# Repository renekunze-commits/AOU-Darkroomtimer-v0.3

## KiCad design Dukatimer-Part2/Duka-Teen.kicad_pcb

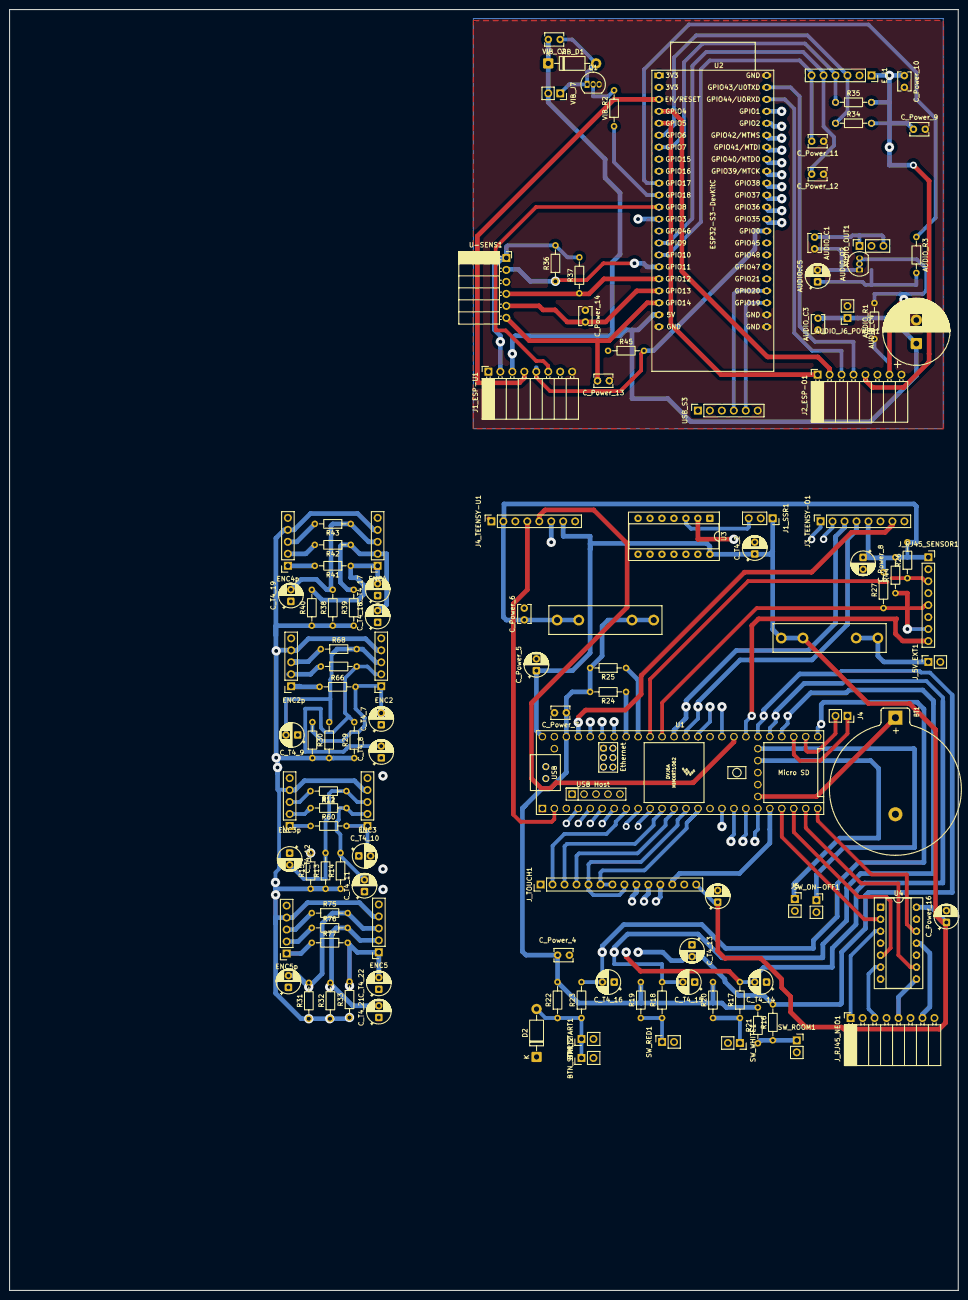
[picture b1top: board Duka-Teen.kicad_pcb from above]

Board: 6 copper layers, 201.3 x 271.8 mm, 122 parts (0 on the bottom side), 89 nets.

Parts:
AUDIO:C5: 10µF; CP_Radial_D5.0mm_P2.50mm
AUDIO_C1: 10nF; C_Disc_D3.8mm_W2.6mm_P2.50mm
AUDIO_C3: 100nF; C_Disc_D3.8mm_W2.6mm_P2.50mm
AUDIO_C4: 1000µF; CP_Radial_D14.0mm_P5.00mm
AUDIO_J6_POWER1: Conn_01x02_Socket; PinSocket_1x02_P2.54mm_Vertical
AUDIO_OUT1: Conn_01x03_Socket; PinSocket_1x03_P2.54mm_Vertical
AUDIO_Q2: BC337; TO-92_Inline
AUDIO_R1: 1k; R_Axial_DIN0204_L3.6mm_D1.6mm_P7.62mm_Horizontal
AUDIO_R3: 10k; R_Axial_DIN0204_L3.6mm_D1.6mm_P7.62mm_Horizontal
BT1: Battery_Cell; BatteryHolder_Keystone_106_1x20mm
BTN_START1, BTN_START2: Conn_01x02_Socket; PinHeader_1x02_P2.54mm_Vertical
C_Power_4, C_Power_6, C_Power_7, C_Power_9, C_Power_10: 100nF; C_Disc_D3.8mm_W2.6mm_P2.50mm
C_Power_5, C_Power_8: 10µF; CP_Radial_D5.0mm_P2.50mm
C_Power_11, C_Power_12, C_Power_13, C_Power_14: NC; C_Disc_D3.8mm_W2.6mm_P2.50mm
C_Power_15, C_Power_16: 100nF; CP_Radial_D5.0mm_P2.50mm
C_T4_2, C_T4_7, C_T4_8, C_T4_9, C_T4_10, C_T4_12, C_T4_13, C_T4_14, C_T4_15, C_T4_16, C_T4_17, C_T4_18, C_T4_19, C_T4_20, C_T4_21, C_T4_22: 100nF; CP_Radial_D5.0mm_P2.50mm
C_T4_11: 10nF; CP_Radial_D5.0mm_P2.50mm
D2: TVS NC; D_DO-41_SOD81_P10.16mm_Horizontal
ENC2, ENC2p, ENC3, ENC3p, ENC4, ENC4p, ENC5, ENC5p: Conn_01x05_Socket; PinSocket_1x05_P2.54mm_Vertical
E_J1: Conn_01x06_Socket; PinSocket_1x06_P2.54mm_Vertical
F3: Fuse_Small; Fuseholder_Littelfuse_100_series_5x20mm
F_5V_EXT1: Fuse_Small; Fuseholder_Littelfuse_100_series_5x20mm
J1_ESP-U1, J2_ESP-O1: Conn_01x08_Socket; PinSocket_1x08_P2.54mm_Horizontal
J1_SSR1: Conn_01x03_Socket; PinSocket_1x03_P2.54mm_Vertical
J3_TEENSY-O1, J4_TEENSY-U1: Conn_01x08_Pin; PinSocket_1x08_P2.54mm_Vertical
J4, J5: Conn_01x02_Socket; PinSocket_1x02_P2.54mm_Vertical
J_5V_EXT1: Screw_Terminal_01x02; PinSocket_1x02_P2.54mm_Vertical
J_RJ45_NEO1: Conn_01x08_Socket; PinSocket_1x08_P2.54mm_Horizontal
J_RJ45_SENSOR1: Conn_01x08_Socket; PinSocket_1x08_P2.54mm_Vertical
J_TOUCH1: Conn_01x14_MountingPin; PinHeader_1x14_P2.54mm_Vertical
Q1: BC337; TO-92_Inline
R11, R12, R41, R42, R43, R60, R66, R67, R68, R75, R76, R77: 100; R_Axial_DIN0204_L3.6mm_D1.6mm_P7.62mm_Horizontal
R13, R19, R20, R21, R22, R24, R25, R26, R27, R28, R29, R30, R33, R38, R45: 10k; R_Axial_DIN0204_L3.6mm_D1.6mm_P7.62mm_Horizontal
R14, R15, R31, R32, R34, R35, R36, R37: NC; R_Axial_DIN0204_L3.6mm_D1.6mm_P7.62mm_Horizontal
R16, R17, R18: 0.8k-2k; R_Axial_DIN0204_L3.6mm_D1.6mm_P7.62mm_Horizontal
R23: 1k-4.7k; R_Axial_DIN0204_L3.6mm_D1.6mm_P7.62mm_Horizontal
R39, R40: 0; R_Axial_DIN0204_L3.6mm_D1.6mm_P7.62mm_Horizontal
R44: 4.7k; R_Axial_DIN0204_L3.6mm_D1.6mm_P7.62mm_Horizontal
SW_ON-OFF1: Conn_01x02_Socket; PinSocket_1x02_P2.54mm_Vertical
SW_RED1: Conn_01x02_Socket; PinSocket_1x02_P2.54mm_Vertical
SW_ROOM1: Conn_01x02_Socket; PinSocket_1x02_P2.54mm_Vertical
SW_WHITE1: Conn_01x02_Socket; PinSocket_1x02_P2.54mm_Vertical
U1: Teensy4.1; Teensy41
U2: ESP32-S3-DevKitC
U3, U4: 74HCT125; CERDIP-14_W7.62mm_SideBrazed_Socket
U-SENS1: Conn_01x06_Socket; PinSocket_1x06_P2.54mm_Horizontal
USB_S3: Conn_01x06_Socket; PinSocket_1x06_P2.54mm_Vertical
VIB_C2: 10nF; C_Disc_D3.8mm_W2.6mm_P2.50mm
VIB_D1: 1N4007; D_DO-41_SOD81_P10.16mm_Horizontal
VIB_J7: Conn_01x02_Socket; PinSocket_1x02_P2.54mm_Vertical
VIB_R2: 1k; R_Axial_DIN0204_L3.6mm_D1.6mm_P7.62mm_Horizontal

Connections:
1W_DATA: J1_ESP-U1.6, J4_TEENSY-U1.6, J_RJ45_SENSOR1.7, R44.1, U2.12 (GPIO8/ADC1_CH7)
+3.3V: C_Power_4.1, C_Power_7.1, C_Power_9.1, C_Power_10.1, ENC2.4, ENC2p.4, ENC3.4, ENC3p.4, ENC4.4, ENC4p.4, ENC5.4, ENC5p.4, E_J1.1, F3.2, J1_ESP-U1.2, J2_ESP-O1.5, R13.1, R14.1, R15.1, R19.2, R20.2, R21.2, R22.2, R24.2, R25.2, R28.1, R29.1, R30.1, R31.1, R32.1, R33.1, R34.2, R35.2, R36.2, R37.2, R38.1, R39.1, R40.1, R45.1, U1.15 (3V3), U1.46 (3V3), U1.51 (3V3), U-SENS1.1
+5V_EXT: AUDIO_C3.2, AUDIO_C4.1, AUDIO_J6_POWER1.1, C_Power_5.1, C_Power_15.1, C_Power_16.1, C_T4_2.1, F_5V_EXT1.2, J1_ESP-U1.3, J1_SSR1.1, J4_TEENSY-U1.3, J4_TEENSY-U1.7, J_TOUCH1.14, U1.48 (VIN), U2.21 (5V), U3.14 (VCC), U4.14 (VCC), VIB_C2.2, VIB_D1.1 (K), VIB_J7.2
+5V_S: F_5V_EXT1.1, J_5V_EXT1.1 (+5V_EXT)
/ESP/AUDIO_SDN: AUDIO:C5.1, AUDIO_Q2.2 (B), AUDIO_R3.2
/ESP/AUDIO_SHDN: AUDIO_R3.1, U2.10 (GPIO17/ADC2_CH6)
/ESP/ENC4_A: C_T4_17.2, ENC4.1, R40.2, R41.1, U2.13 (GPIO3/ADC1_CH2)
/ESP/ENC4_Ap: ENC4p.1, R41.2
/ESP/ENC4_B: C_T4_18.2, ENC4.2, R39.2, R42.1, U2.40 (GPIO2/ADC1_CH1)
/ESP/ENC4_Bp: ENC4p.2, R42.2
/ESP/ENC4_SW: C_T4_19.2, ENC4.3, R38.2, R43.1, R43.2, U2.41 (GPIO1/ADC1_CH0)
/ESP/PWM_L: AUDIO_C1.1, AUDIO_OUT1.1, AUDIO_OUT1.3
/ESP/S3_GPIO06: E_J1.3, R34.1, R35.1, U2.6 (GPIO6/ADC1_CH5)
/ESP/S3_GPIO09: C_Power_12.2, E_J1.5, U2.15 (GPIO9/ADC1_CH8)
/ESP/S3_GPIO10: C_Power_11.2, E_J1.6, U2.16 (GPIO10/ADC1_CH9)
/ESP/S3_GPIO11-SDA-AHT: R36.1, U2.17 (GPIO11/ADC2_CH0), U-SENS1.2
/ESP/S3_GPIO12-ACL-AHT: R37.1, U2.18 (GPIO12/ADC2_CH1)
/ESP/S3_GPIO13: C_Power_14.2, U2.19 (GPIO13/ADC2_CH2), U-SENS1.5
/ESP/S3_GPIO14: C_Power_13.2, U2.20 (GPIO14/ADC2_CH3), U-SENS1.6
/ESP/VIB_PWM: U2.11 (GPIO18/ADC2_CH7), VIB_R2.1
/teensy/+3V3_HEAD: C_Power_6.1, C_Power_8.1, F3.1, J4_TEENSY-U1.2, J_RJ45_SENSOR1.1, R26.2, R27.2, R44.2
/teensy/BTN_START: C_T4_16.2, R23.2, U1.25 (33_MCLK2)
/teensy/ENC1_A: C_T4_20.2, ENC5.3, R31.2, R75.2, U1.4 (2_OUT2)
/teensy/ENC1_Ap: ENC5p.3, R75.1
/teensy/ENC1_B: C_T4_21.2, ENC5.2, R32.2, R76.2, U1.5 (3_LRCLK2)
/teensy/ENC1_Bp: ENC5p.2, R76.1
/teensy/ENC1_SW: C_T4_22.2, ENC5.1, R33.2, R77.2, U1.6 (4_BCLK2)
/teensy/ENC1_SWp: ENC5p.1, R77.1
/teensy/ENC2_A: C_T4_7.2, ENC2.1, R28.2, R66.2, U1.7 (5_IN2)
/teensy/ENC2_Ap: ENC2p.1, R66.1
/teensy/ENC2_B: C_T4_8.2, ENC2.2, R29.2, R67.2, U1.43 (21_A7_RX5_BCLK1)
/teensy/ENC2_Bp: ENC2p.2, R67.1
/teensy/ENC2_SW: C_T4_9.2, ENC2.3, R30.2, R68.2, U1.42 (20_A6_TX5_LRCLK1)
/teensy/ENC2_SWp: ENC2p.3, R68.1
/teensy/ENC3_A: C_T4_10.2, ENC3.1, R60.2, U1.17 (25_A11_RX6_SDA2)
/teensy/ENC3_Ap: ENC3p.1, R15.2, R60.1
/teensy/ENC3_B: C_T4_11.2, ENC3.2, R11.2, R14.2, U1.18 (26_A12_MOSI1)
/teensy/ENC3_Bp: ENC3p.2, R11.1
/teensy/ENC3_SW: C_T4_12.2, ENC3.3, R12.1, R13.2, U1.19 (27_A13_SCK1)
/teensy/I2C0_SCL: R24.1, U1.41 (19_A5_SCL)
/teensy/I2C0_SDA: R25.1, U1.40 (18_A4_SDA)
/teensy/I2C1_SCL: J_RJ45_SENSOR1.5, R27.1, U1.38 (16_A2_RX4_SCL1)
/teensy/I2C1_SDA: J_RJ45_SENSOR1.3, R26.1, U1.39 (17_A3_TX4_SDA1)
/teensy/NEO_1: U1.21 (29_TX7), U4.2 (1A)
/teensy/NEO_2: U1.23 (31_CTX3), U4.9 (3A)
/teensy/NEO_3: U1.22 (30_CRX3), U4.5 (2A)
/teensy/PIN_BTN_RED: C_T4_15.2, R18.2, U1.28 (36_CS)
/teensy/PIN_BTN_ROOM: C_T4_13.2, R16.2, U1.30 (38_CS1_IN1)
/teensy/PIN_BTN_WHITE: C_T4_14.2, R17.2, U1.29 (37_CS)
/teensy/SPI_MISO: J_TOUCH1.6, J_TOUCH1.7, U1.14 (12_MISO_MQSL)
/teensy/SPI_MOSI: J_TOUCH1.5, J_TOUCH1.8, U1.13 (11_MOSI_CTX1)
/teensy/SPI_SCK: J_TOUCH1.9, U1.35 (13_SCK_LED)
/teensy/SSR_ROOM: U1.16 (24_A10_TX6_SCL2), U3.2 (1A)
/teensy/SSR_ROOM_5V: J1_SSR1.3, U3.3 (1Y)
/teensy/TFT_BL: J_TOUCH1.10, U1.44 (22_A8_CTX1)
/teensy/TFT_CS: J_TOUCH1.4, U1.12 (10_CS_MQSR)
/teensy/TFT_DC: J_TOUCH1.3, U1.11 (9_OUT1C)
/teensy/TFT_RST: J_TOUCH1.11, U1.33 (41_A17)
/teensy/TOUCH_CS: J_TOUCH1.2, U1.8 (6_OUT1D)
/teensy/TOUCH_IRQ: J_TOUCH1.12, U1.20 (28_RX7)
/teensy/TSL_INT: J_RJ45_SENSOR1.8, U1.31 (39_MISO1_OUT1A)
AUDIO_PWM: J2_ESP-O1.7, J3_TEENSY-O1.7, U1.45 (23_A9_CRX1_MCLK1)
ENC3_SWp: ENC3p.3, R12.2
GND: AUDIO:C5.2, AUDIO_C1.2, AUDIO_C3.1, AUDIO_C4.2, AUDIO_J6_POWER1.2, AUDIO_OUT1.2, AUDIO_Q2.1 (C), AUDIO_Q2.3 (E), AUDIO_R1.1, AUDIO_R1.2, BT1.2 (-), BTN_START1.2, BTN_START2.2, C_Power_4.2, C_Power_5.2, C_Power_6.2, C_Power_7.2, C_Power_8.2, C_Power_9.2, C_Power_10.2, C_Power_11.1, C_Power_12.1, C_Power_13.1, C_Power_14.1, C_Power_15.2, C_Power_16.2, C_T4_2.2, C_T4_7.1, C_T4_8.1, C_T4_9.1, C_T4_10.1, C_T4_11.1, C_T4_12.1, C_T4_13.1, C_T4_14.1, C_T4_15.1, C_T4_16.1, C_T4_17.1, C_T4_18.1, C_T4_19.1, C_T4_20.1, C_T4_21.1, C_T4_22.1, D2.1 (K), ENC2.5, ENC2p.5, ENC3.5, ENC3p.5, ENC4.5, ENC4p.5, ENC5.5, ENC5p.5, E_J1.2, J1_ESP-U1.1, J1_ESP-U1.8, J1_SSR1.2, J2_ESP-O1.8, J3_TEENSY-O1.8, J4_TEENSY-U1.1, J4_TEENSY-U1.8, J5.2, J_5V_EXT1.2 (GND), J_RJ45_NEO1.2, J_RJ45_NEO1.4, J_RJ45_NEO1.6, J_RJ45_NEO1.8, J_RJ45_SENSOR1.2, J_RJ45_SENSOR1.4, J_RJ45_SENSOR1.6, J_TOUCH1.1, J_TOUCH1.13, Q1.3 (E), SW_ON-OFF1.2, SW_RED1.2, SW_ROOM1.2, SW_WHITE1.2, U1.1 (GND), U1.34 (GND), U1.47 (GND), U1.52 (GND), U2.22 (GND), U2.23 (GND), U2.24 (GND), U2.44 (GND), U3.1 (1~OE), U3.4 (2~OE), U3.5 (2A), U3.7 (GND), U3.9 (3A), U3.10 (3~OE), U3.12 (4A), U3.13 (4~OE), U4.1 (1~OE), U4.4 (2~OE), U4.7 (GND), U4.10 (3~OE), U4.13 (4~OE), U-SENS1.3, USB_S3.2, USB_S3.6
NEO_4: U1.24 (32_OUT1B), U4.12 (4A)
unnamed: BT1.1 (+), U1.50 (VBAT)
unnamed: BTN_START1.1, BTN_START2.1, D2.2 (A), R22.1, R23.1
unnamed: J4.1, U1.27 (35_TX8)
unnamed: J4.2, U1.26 (34_RX8)
unnamed: J5.1, U1.53 (PROGRAM)
unnamed: J_RJ45_NEO1.1, U4.3 (1Y)
unnamed: J_RJ45_NEO1.3, U4.6 (2Y)
unnamed: J_RJ45_NEO1.5, U4.8 (3Y)
unnamed: J_RJ45_NEO1.7, U4.11 (4Y)
unnamed: Q1.2 (B), VIB_R2.2
unnamed: Q1.1 (C), VIB_C2.1, VIB_D1.2 (A), VIB_J7.1
unnamed: SW_ON-OFF1.1, U1.54 (ON_OFF)
unnamed: R18.1, R19.1, SW_RED1.1
unnamed: R16.1, R21.1, SW_ROOM1.1
unnamed: R17.1, R20.1, SW_WHITE1.1
unnamed: U2.25 (GPIO19/USB_D-), USB_S3.5
unnamed: U2.26 (GPIO20/USB_D+), USB_S3.4
S3_CTS: J2_ESP-O1.1, J3_TEENSY-O1.1, U1.10 (8_TX2_IN1), U2.5 (GPIO5/ADC1_CH4)
S3_EN_RST: J1_ESP-U1.4, J4_TEENSY-U1.4, U1.2 (0_RX1_CRX2_CS1), U2.3 (CHIP_PU)
S3_GPIO0: J1_ESP-U1.5, J4_TEENSY-U1.5, R45.2, U1.32 (40_A16), U2.31 (GPIO0)
S3_GPIO07: E_J1.4, U2.7 (GPIO7/ADC1_CH6)
S3_RTS: J2_ESP-O1.2, J3_TEENSY-O1.2, U1.9 (7_RX2_OUT1A), U2.4 (GPIO4/ADC1_CH3)
S3_RX: J2_ESP-O1.3, J3_TEENSY-O1.4, U1.36 (14_A0_TX3_SPDIF_OUT), U2.42 (GPIO44/U0RXD)
S3_TX: J2_ESP-O1.4, J3_TEENSY-O1.3, U1.37 (15_A1_RX3_SPDIF_IN), U2.43 (GPIO43/U0TXD)

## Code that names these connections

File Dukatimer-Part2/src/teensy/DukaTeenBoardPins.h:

#pragma once

#include <stdint.h>

namespace dukatimer {
namespace board {

// Spiegel der aktuellen Teensy-Pintabelle aus
// docs/hardware/duka-teen-schematic-overview.md. Wenn sich das PCB- oder
// Schaltplanrouting aendert, muss diese Datei bewusst mitgezogen werden, damit
// die produktive Verdrahtung nicht still in main.cpp auseinanderlaeuft.
constexpr uint8_t PIN_ENC1_A = 2;
constexpr uint8_t PIN_ENC1_B = 3;
constexpr uint8_t PIN_ENC1_SW = 4;
constexpr uint8_t PIN_ENC2_A = 5;
constexpr uint8_t PIN_TOUCH_CS = 6;
constexpr uint8_t PIN_S3_RTS = 7;
constexpr uint8_t PIN_S3_CTS = 8;
constexpr uint8_t PIN_TFT_DC = 9;
constexpr uint8_t PIN_TFT_CS = 10;
constexpr uint8_t PIN_SSR_ROOM = 24;
constexpr uint8_t PIN_ENC3_A = 25;
constexpr uint8_t PIN_ENC3_B = 26;
constexpr uint8_t PIN_ENC3_SW = 27;
constexpr uint8_t PIN_TOUCH_IRQ = 28;
constexpr uint8_t PIN_NEO_1 = 29;
constexpr uint8_t PIN_NEO_2 = 30;
constexpr uint8_t PIN_NEO_3 = 31;
constexpr uint8_t PIN_NEO_4 = 32;
constexpr uint8_t PIN_BTN_START = 33;
constexpr uint8_t PIN_BTN_RED = 36;
constexpr uint8_t PIN_BTN_WHITE = 37;
constexpr uint8_t PIN_BTN_ROOM = 38;
constexpr uint8_t PIN_TSL_INT = 39;
constexpr uint8_t PIN_S3_GPIO0 = 40;
constexpr uint8_t PIN_TFT_RST = 41;
constexpr uint8_t PIN_ENC2_SW = 20;
constexpr uint8_t PIN_ENC2_B = 21;
constexpr uint8_t PIN_TFT_BL = 22;

}  // namespace board
}  // namespace dukatimer

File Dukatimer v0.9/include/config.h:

/* =============================================================================
 * Config.h - DUKATIMER BETA (v0.916.8)
 * * ZENTRALE HARDWARE-KONFIGURATION (Exakt v0.5 Wiring)
 * * HÄRTUNG: Pegel-Definitionen für Schalter und Relais.
 * ========================================================================== */

#pragma once
#include <Arduino.h>

#define SW_VERSION_NAME "v0.916.8 Beta"
#define SW_VERSION_HEX 0x0916 

#define NVS_SPACE "dukatimer"

// =============================================================================
// 1. BENUTZERSCHNITTSTELLE (EINGABEN) - Exakt v0.5 Layout
// =============================================================================

// Encoder 1: Soft (Links)
#define PIN_ENC_SOFT_A  5
#define PIN_ENC_SOFT_B  4
#define PIN_ENC_SOFT_SW 42 

// Encoder 2: Hard (Mitte Links)
#define PIN_ENC_HARD_A  6
#define PIN_ENC_HARD_B  7
#define PIN_ENC_HARD_SW 41 

// Encoder 3: Grade (Mitte Rechts)
#define PIN_ENC_GRADE_A 15
#define PIN_ENC_GRADE_B 16
#define PIN_ENC_GRADE_SW 39 

// Encoder 4: Mode (Rechts / Master)
#define PIN_ENC_MODE_A  40
#define PIN_ENC_MODE_B  47 
#define PIN_ENC_MODE_SW 3 

// Mechanische Schalter & Taster (Inputs)
// WICHTIG: Diese Schalter ziehen in deinem v0.5 Layout gegen GND.
#define PIN_BTN_START 11 
#define PIN_BTN_RED   21   // Savelight Schalter (Eingang)
#define PIN_BTN_WHITE 14   // Focus Schalter (Eingang)
#define PIN_BTN_ROOM  13   // Raumlicht Schalter (Eingang)

// =============================================================================
// 2. AKTOREN (AUSGÄNGE)
// =============================================================================
#define PIN_NEOPIXEL   38    
#define NEOPIXEL_COUNT 256 

// Relais-Steuerung
// Pin 12 ist das einzige Relais (Raumlicht).
#define PIN_RELAY_ROOMLIGHT 12
//#define PIN_RELAY_FOCUS     -1
//#define PIN_RELAY_SAFE      -1
//#define PIN_RELAY_ENLARGER  -1

// Buzzer (Auf Pin 45 verschoben, da Pin 36/37 beim S3 Octal-RAM kritisch sind)
#define PIN_BUZZER 45 

// =============================================================================
// 3. KOMMUNIKATION & SENSORIK
// =============================================================================
#define NEXTION_TX 2
#define NEXTION_RX 1

#define I2C_SDA  8
#define I2C_SCL  9
#define I2C_FREQ 100000 

#define ADDR_LCD     0x3E     
#define ADDR_TSL2591 0x29 
#define ADDR_BMP280  0x76  

#define PIN_I2C1_SDA 17
#define PIN_I2C1_SCL 18
#define I2C1_FREQ    400000 

#define ADDR_TSL2561    0x39  
#define PIN_TSL2561_INT 46  

#define PIN_ONEWIRE 10

// =============================================================================
// 4. SOFTWARE PARAMETER
// =============================================================================
#define kStateLockWait pdMS_TO_TICKS(100)
#define kDoseLockWait  pdMS_TO_TICKS(100)
#define kPreWaitMs 500U

#define TIME_MIN_S 0.5
#define TIME_MAX_S 999.0
#define TEMP_MAX_ALU 60.0
#define SOUND_QUIET_SCALE 0.60

static const char* const stepNames[] = {"1/1", "1/2", "1/3", "1/6"};

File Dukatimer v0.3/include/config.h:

#ifndef CONFIG_H
#define CONFIG_H

#include <Arduino.h>

// =============================================================================
// CONFIG.H - Zentrale Hardware- und Software-Konstanten (v0.5)
// =============================================================================

// --- ENCODER ---
#define ENC_SOFT_A      5
#define ENC_SOFT_B      4
#define ENC_HARD_A      6
#define ENC_HARD_B      7
#define ENC_GRADE_A     15
#define ENC_GRADE_B     16

// NEU: Master Mode Encoder (PCNT 3)
#define ENC_MODE_A      40 // Ehemaliger Pin für PIN_SW_DOSEMODE
#define ENC_MODE_B      47 // ACHTUNG: Bitte prüfen, ob Pin 19 auf dem S3-Board frei ist!

// Encoder Taster (Physische Belegung)
#define PIN_SW_ENTER    41  // Encoder 2 Klick (Tatsächlich auf 41)
#define PIN_SW_BACK     42  // Encoder 1 Klick (Tatsächlich auf 42)
#define PIN_SW_GRADE    39  // Encoder 3 Klick
#define PIN_SW_MODE     3   // ACHTUNG: Bitte prüfen, ob Pin 3 auf dem S3-Board frei ist!

// Logische Aliase (Vermeidung von Doppelbelegungen)
#define PIN_SW_STEP_SELECT  PIN_SW_BACK 

// --- DISPLAYS ---
#define NEXTION_RX      1 
#define NEXTION_TX      2 

// --- I2C BUSSE ---
#define PIN_I2C0_SDA     8
#define PIN_I2C0_SCL     9
#define I2C0_FREQ        100000  
#define LCD_I2C_ADDR     0x3E  
#define TSL2591_I2C_ADDR 0x29  
#define BMP280_I2C_ADDR  0x76  // <--- Hier ist der Umgebungstemp-Sensor!

#define PIN_I2C1_SDA     17
#define PIN_I2C1_SCL     18
#define I2C1_FREQ        400000 
#define TSL2561_I2C_ADDR 0x39  

// --- SENSOREN ---
#define PIN_ONEWIRE     10  
#define PIN_TSL2561_INT 46  

// --- MECHANISCHE SCHALTER (INPUTS) ---
#define PIN_START           11  
#define PIN_SW_ROOMLIGHT    13  
#define PIN_SW_FOCUS        14  
#define PIN_SW_SAFE         21  

// HINWEIS: PIN_SW_DOSEMODE wurde durch den Mode-Encoder ersetzt!

// --- AUSGÄNGE ---
#define PIN_RELAY_ROOMLIGHT 12 
#undef  PIN_NEOPIXEL
#define PIN_NEOPIXEL        38    
#define NEOPIXEL_COUNT      256 
#define PIN_BUZZER          36  
//#define PIN_RELAY_SAFE      22
//#define PIN_RELAY_ENLARGER  23
//#define PIN_RELAY_SAFE      1
//#define PIN_RELAY_ENLARGER  2



// =============================================================================
// SOFTWARE KONFIGURATION
// =============================================================================
#define SW_VERSION 0x0500

// CODE_REVIEW FIX (Audit Kritisch #12): ODR-Verletzung behoben.
// 'const String stepNames[]' in einem Header erzeugt pro Translation Unit eine eigene
// Kopie mit separaten Konstruktor-Aufrufen (Arduino String ist kein Literal-Typ).
// Das verschwendet RAM und erzeugt unnötige Runtime-Initialisierung.
// Fix: Statische const char* Zeiger-Tabelle. Kein Konstruktor, kein ODR-Problem.
// const String stepNames[] = {"1/1", "1/2", "1/3", "1/6"};  // ALT: ODR-Verletzung
static const char* const stepNames[] = {"1/1", "1/2", "1/3", "1/6"};

#define TIME_MIN_S      0.5
#define TIME_MAX_S      999.0

#define DEFAULT_TS_N    6
#define DEFAULT_TS_EV   (1.0/3.0)
#define TS_EV_MIN       0.1
#define TS_EV_MAX       1.0
#define TS_EV_STEP      (1.0/6.0)

#define SOUND_QUIET_SCALE 0.60
#define TEMP_MAX_ALU    60.0
#define FILTER_SIZE     10 

#endif

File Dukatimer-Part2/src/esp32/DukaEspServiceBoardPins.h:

#pragma once

#include <stdint.h>

namespace dukatimer {
namespace esp_board {

// Spiegel der aktuell dokumentierten ESP32-S3-Servicebelegung aus
// docs/hardware/duka-teen-schematic-overview.md. Wenn sich die KiCad-Revision
// aendert, muessen UART-, Sensor- und spaetere Encoder4-Pins hier gemeinsam
// nachgezogen werden statt verteilt in mehreren Diensten.
constexpr int PIN_UART_RX = 44;
constexpr int PIN_UART_TX = 43;
constexpr int PIN_UART_CTS = 5;
constexpr int PIN_UART_RTS = 4;

constexpr uint8_t PIN_ONEWIRE = 8;
// Der Umweltsensorbus auf U-SENS1 ist ein gemeinsamer I2C-Pfad fuer AHT20 und
// BMP280. Beide Sensoren teilen sich diese Leitungen und werden gemeinsam als
// Servicepfad zum Teensy publiziert.
constexpr uint8_t PIN_AHT_SDA = 11;
constexpr uint8_t PIN_AHT_SCL = 12;

// Encoder 4 liegt lokal auf dem ESP32-S3 und wird als stoerungsarmer
// Kontextencoder per PCNT erfasst. Die semantische Auswertung bleibt trotzdem
// auf Teensy-Seite ueber den bestehenden Remote-Input-Pfad gebuendelt.
constexpr uint8_t PIN_ENC4_A = 3;
constexpr uint8_t PIN_ENC4_B = 2;
constexpr uint8_t PIN_ENC4_SW = 1;

}  // namespace esp_board
}  // namespace dukatimer

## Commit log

2026-02-16 Sauberer Neuimport aller Projekte
2026-02-16 Add project README
2026-02-22 Implement shadow vs highlight contrast measurement logic, fix variable scope issues, and update ESP-NOW OLED render function.
2026-02-22 Initial import (AOU Darkroomtimer v0.3 full project)
2026-05-21 docs: add NeoPixelHead timing instrumentation docs and changelog
2026-05-21 Upload kompletter Workspace-Stand
